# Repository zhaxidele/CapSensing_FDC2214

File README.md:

# CapSensing_FDC2214
This a compact toolkit of capacitive sensing based on FDC2214 from Texas Instrument.

Sources including the hardware files of a capacitive sensing board with FDC2214, the driver files of FDC2214, the firmware code using Arduino BLE Nano as the mother board(of course suitable for other open source boards, even no need for any modification at all.)

Feel free to use and comment.

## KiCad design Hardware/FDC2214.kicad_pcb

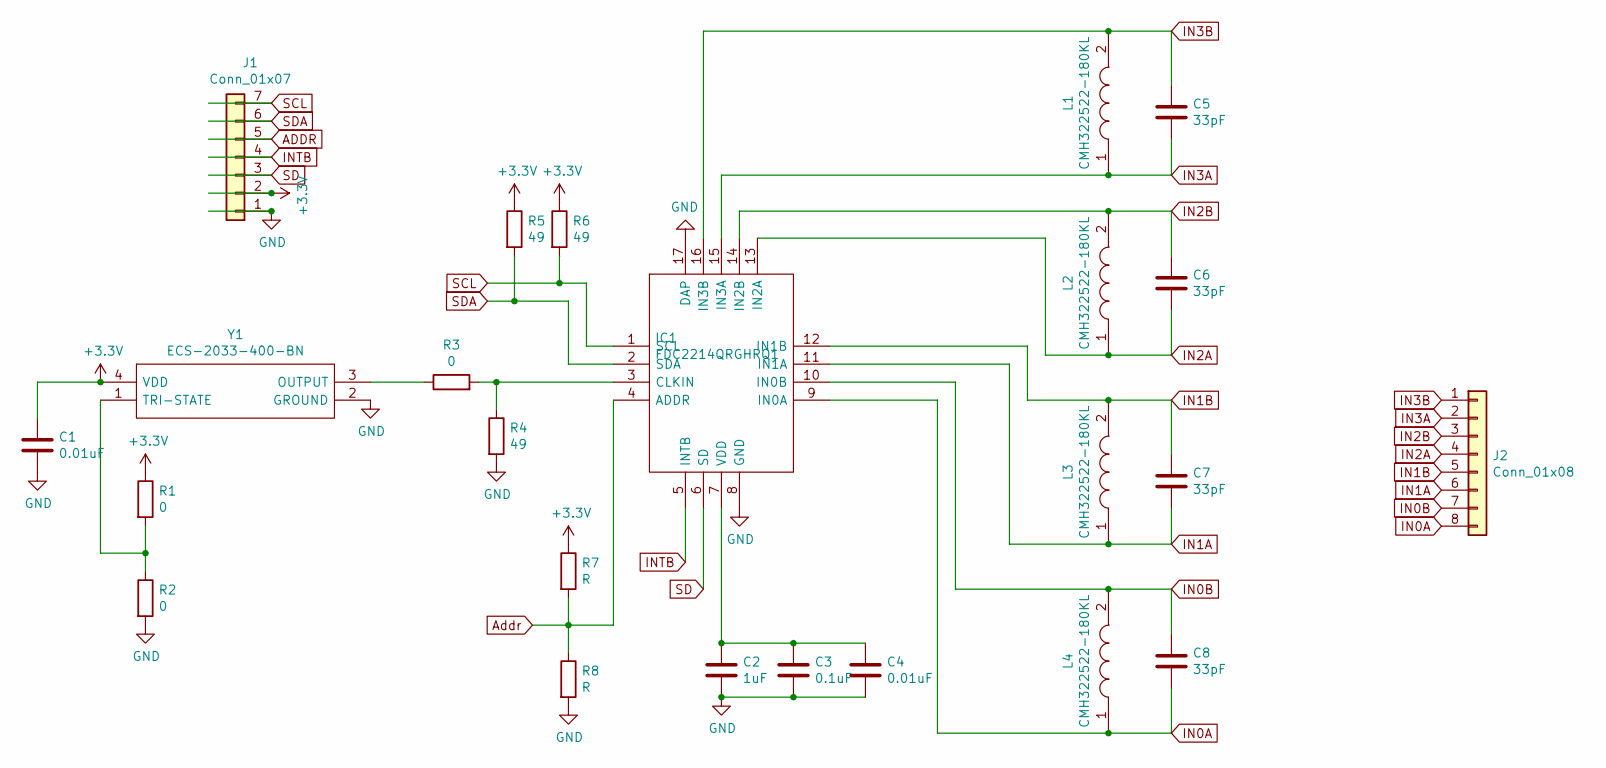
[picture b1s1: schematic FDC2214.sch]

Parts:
C1, C4: 0.01uF; C_0603_1608Metric
C2: 1uF; C_0603_1608Metric
C3: 0.1uF; C_0603_1608Metric
C5, C6, C7, C8: 33pF; C_0603_1608Metric
IC1: FDC2214QRGHRQ1; QFN50P400X400X80-17N; Manufacturer_Part_Number FDC2214QRGHRQ1; Mouser Part Number 595-FDC2214QRGHRQ1
J1: Conn_01x07; PinHeader_1x07_P2.54mm_Vertical
J2: Conn_01x08; PinHeader_1x08_P2.54mm_Vertical
L1, L2, L3, L4: CMH322522-180KL; INDPM3225X240N; Mouser Part Number 652-CMH322522-180KL
R1, R2, R3: 0; R_0603_1608Metric_Pad0.98x0.95mm_HandSolder
R4, R5, R6: 49; R_0603_1608Metric_Pad0.98x0.95mm_HandSolder
R7, R8: R; R_0603_1608Metric_Pad0.98x0.95mm_HandSolder
Y1: ECS-2033-400-BN; ECS2033400BN; Mouser Part Number 520-2033-400-BN

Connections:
+3V3: C1.1, J1.2, R1.1, R5.1, R6.1, R7.1, Y1.4 (VDD)
ADDR: J1.5
Addr: IC1.4 (ADDR), R7.2, R8.1
GND: C1.2, C2.2, C3.2, C4.2, IC1.8 (GND), IC1.17 (DAP), J1.1, R2.2, R4.2, R8.2, Y1.2 (GROUND)
IN0A: C8.2, IC1.9 (IN0A), J2.8, L4.1
IN0B: C8.1, IC1.10 (IN0B), J2.7, L4.2
IN1A: C7.2, IC1.11 (IN1A), J2.6, L3.1
IN1B: C7.1, IC1.12 (IN1B), J2.5, L3.2
IN2A: C6.2, IC1.13 (IN2A), J2.4, L2.1
IN2B: C6.1, IC1.14 (IN2B), J2.3, L2.2
IN3A: C5.2, IC1.15 (IN3A), J2.2, L1.1
IN3B: C5.1, IC1.16 (IN3B), J2.1, L1.2
INTB: IC1.5 (INTB), J1.4
unnamed: C2.1, C3.1, C4.1, IC1.7 (VDD)
unnamed: IC1.3 (CLKIN), R3.2, R4.1
unnamed: R1.2, R2.1, Y1.1 (TRI-STATE)
unnamed: R3.1, Y1.3 (OUTPUT)
SCL: IC1.1 (SCL), J1.7, R6.2
SD: IC1.6 (SD), J1.3
SDA: IC1.2 (SDA), J1.6, R5.2

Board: 2 copper layers, 24 parts (0 on the bottom side), 19 nets, no tracks yet.

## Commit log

2022-01-03 correct the double reading problem when reading two FDC2214
